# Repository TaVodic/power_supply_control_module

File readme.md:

# Laboratory Power Supply Control Module (PSCM)   

Module is an upgarde for Nice-Power SPS305 0-30V/0-5A laboratory power supply. Module use encoders instead of potentiometers. Based on ATmega328PB.
Using arduino-cli framework.  
### Features:
* Encoders EC12E, fine and coarse set of volatge and current
* Digital potentiometers MCP4251
* ATmega328PB
* Sniffing the PS voltage, current and power - providing a feedback
* UART connection for PC connection and automated PS setting

### Libraries used:
* Encoder_mt, [original](https://github.com/PaulStoffregen/Encoder) modified to use PCINT and optimized for the use-case
* DispSniff, sniffing SDI & CLK pins of TM1640 (of the original PS) to capture voltage, current and power values of the PS
* MCP4251, [original](https://github.com/kulbhushanchand/MCP4251)

## [Schematic v1.0.0](docu/pscm_schematic_v1.0.0.pdf)

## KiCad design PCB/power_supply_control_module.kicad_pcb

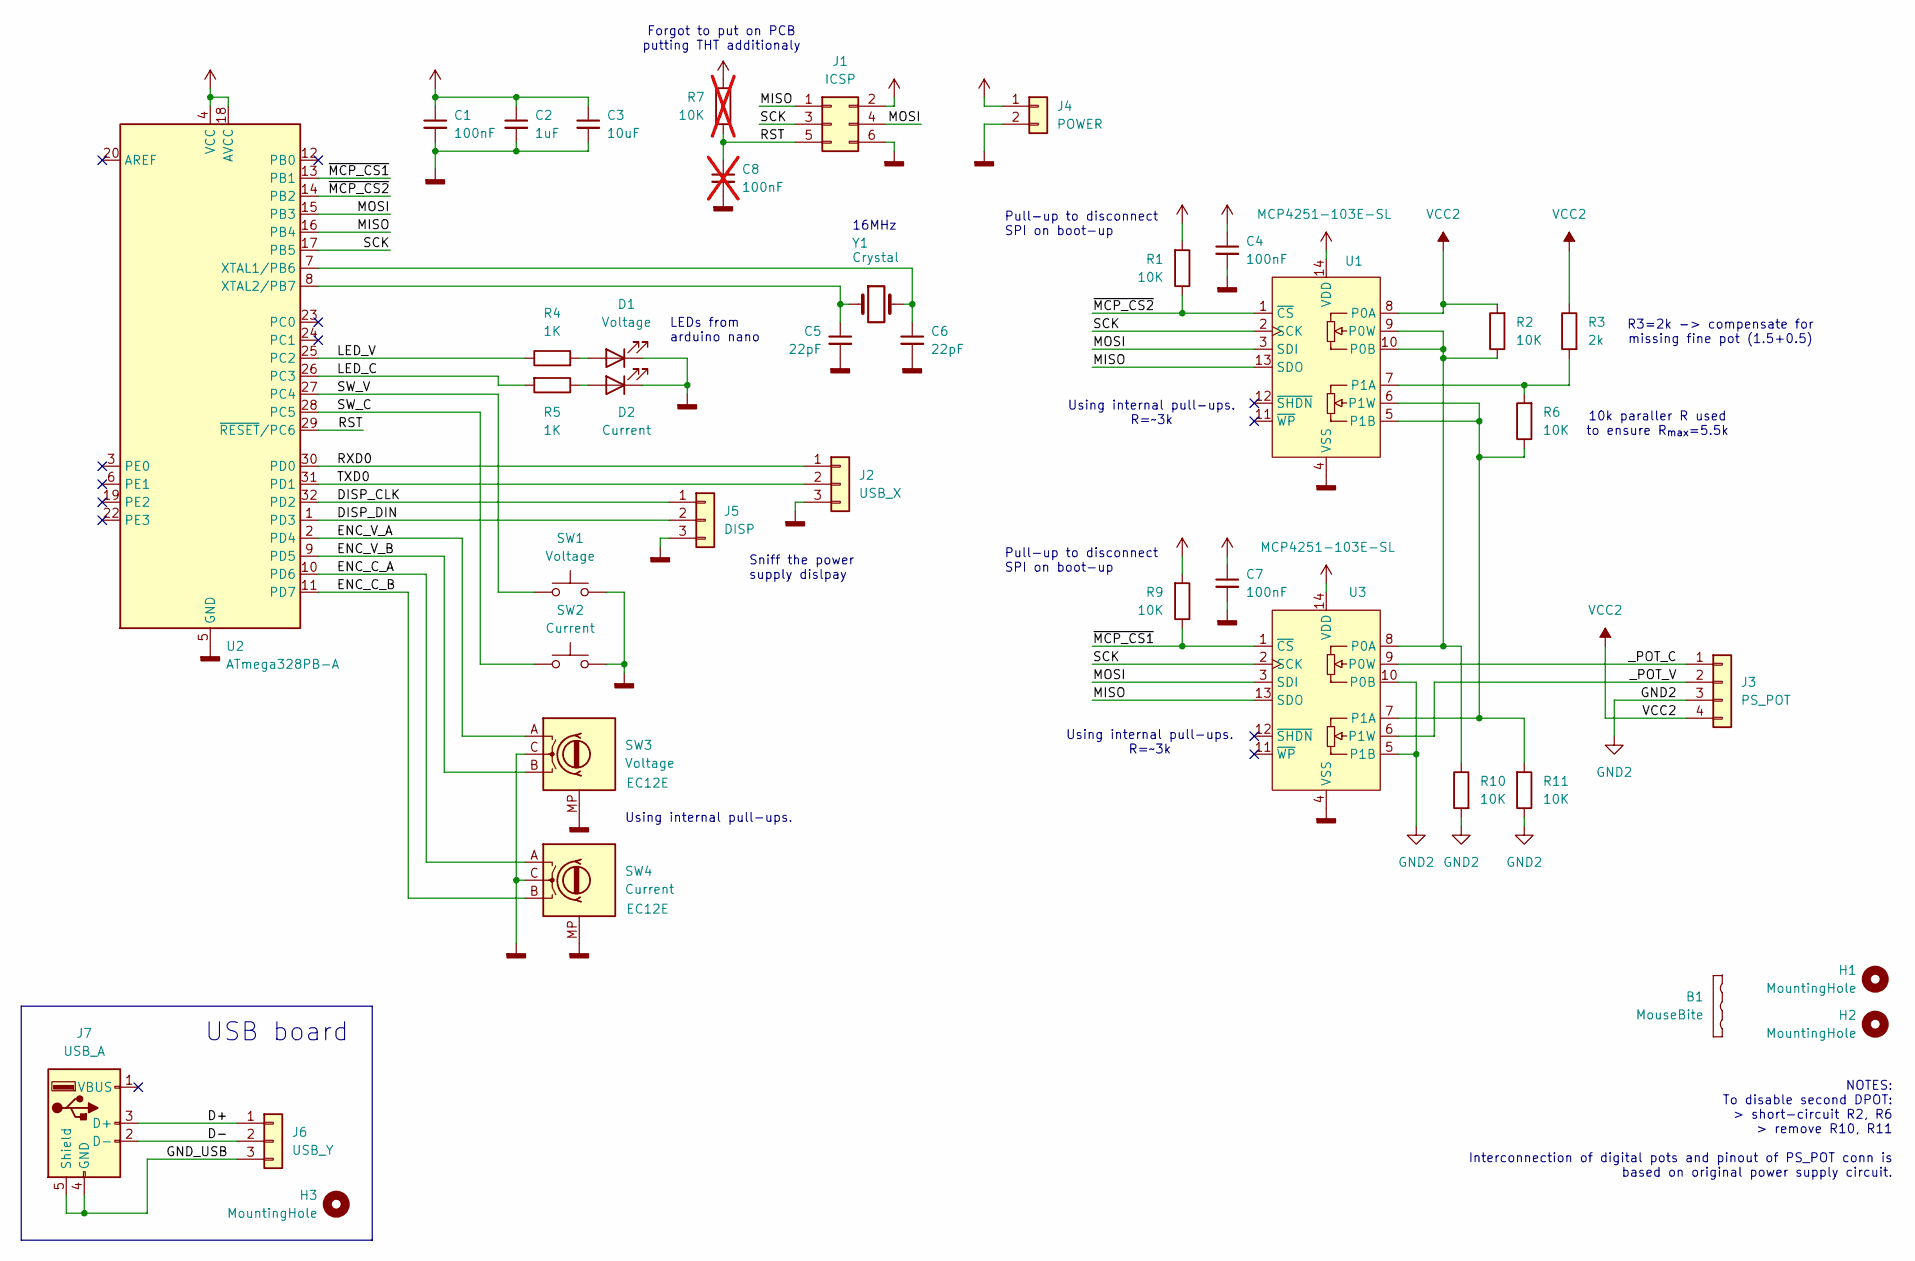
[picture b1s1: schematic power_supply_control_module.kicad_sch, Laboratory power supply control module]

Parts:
B1: MouseBite; mouse-bite-3mm-slot-jlcpcb
C1, C4, C7: 100nF; C_1206_3216Metric_Pad1.33x1.80mm_HandSolder
C2: 1uF; C_1206_3216Metric_Pad1.33x1.80mm_HandSolder
C3: 10uF; C_1206_3216Metric_Pad1.33x1.80mm_HandSolder
C5, C6: 22pF; C_1206_3216Metric_Pad1.33x1.80mm_HandSolder
C8: 100nF; C_1206_3216Metric_Pad1.33x1.80mm_HandSolder; not fitted
D1: Voltage; LED_0603_1608Metric_Pad1.05x0.95mm_HandSolder
D2: Current; LED_0603_1608Metric_Pad1.05x0.95mm_HandSolder
H1, H2, H3: MountingHole; MountingHole_3.2mm_M3_ISO7380
J1: ICSP; PinHeader_2x03_P2.54mm_Vertical
J2: USB_X; SHDR3W50P0X200_1X3_800X470X640P
J3: PS_POT; JST_XH_B4B-XH-A_1x04_P2.50mm_Vertical
J4: POWER; 140502415001
J5: DISP; SHDR3W50P0X200_1X3_800X470X640P
J6: USB_Y; PinHeader_1x03_P2.00mm_Vertical
J7: USB_A; USB_A_Molex_105057_Vertical
R1, R2, R6, R9, R10, R11: 10K; R_1206_3216Metric_Pad1.30x1.75mm_HandSolder
R3: 2k; R_1206_3216Metric_Pad1.30x1.75mm_HandSolder
R4, R5: 1K; R_1206_3216Metric_Pad1.30x1.75mm_HandSolder
R7: 10K; R_1206_3216Metric_Pad1.30x1.75mm_HandSolder; not fitted
SW1: Voltage; SW_TH_Tactile_Omron_B3F-107x
SW2: Current; SW_TH_Tactile_Omron_B3F-107x
SW3: Voltage; RotaryEncoder_Alps_EC12E_Vertical_H20mm
SW4: Current; RotaryEncoder_Alps_EC12E_Vertical_H20mm
U1, U3: MCP4251-103E-SL; SOIC-14_3.9x8.7mm_P1.27mm
U2: ATmega328PB-A; TQFP-32_7x7mm_P0.8mm
Y1: Crystal; Crystal_HC49-4H_Vertical

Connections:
/D+: J6.1, J7.3 (D+)
/D-: J6.2, J7.2 (D-)
/DISP_CLK: J5.1, U2.32 (PD2)
/DISP_DIN: J5.2, U2.1 (PD3)
/ENC_C_A: SW4.A, U2.10 (PD6)
/ENC_C_B: SW4.B, U2.11 (PD7)
/ENC_V_A: SW3.A, U2.2 (PD4)
/ENC_V_B: SW3.B, U2.9 (PD5)
/GND_USB: J6.3, J7.4 (GND), J7.5 (Shield)
/LED_C: R5.2, U2.26 (PC3)
/LED_V: R4.1, U2.25 (PC2)
/MISO: J1.1, U1.13 (SDO), U2.16 (PB4), U3.13 (SDO)
/MOSI: J1.4, U1.3 (SDI), U2.15 (PB3), U3.3 (SDI)
/RST: C8.1, J1.5, R7.1, U2.29 (~RESET/PC6)
/RXD0: J2.1, U2.30 (PD0)
/SCK: J1.3, U1.2 (SCK), U2.17 (PB5), U3.2 (SCK)
/SW_C: SW2.1, U2.28 (PC5)
/SW_V: SW1.1, U2.27 (PC4)
/TXD0: J2.2, U2.31 (PD1)
/_POT_C: J3.1, U3.9 (P0W)
/_POT_V: J3.2, U3.6 (P1W)
/~MCP_CS1: R9.1, U2.13 (PB1), U3.1 (~CS)
/~MCP_CS2: R1.1, U1.1 (~CS), U2.14 (PB2)
GND2: J3.3, R10.2, R11.1, U3.5 (P1B), U3.10 (P0B)
GNDD: C1.2, C2.2, C3.2, C4.2, C5.2, C6.2, C7.2, C8.2, D1.1 (K), D2.1 (K), J1.6, J2.3, J4.2, J5.3, SW1.2, SW2.2, SW3.C, SW3.MP, SW4.C, SW4.MP, U1.4 (VSS), U2.5 (GND), U2.21 (GND), U3.4 (VSS)
unnamed: D1.2 (A), R4.2
unnamed: D2.2 (A), R5.1
unnamed: R2.1, R10.1, U1.9 (P0W), U1.10 (P0B), U3.8 (P0A)
unnamed: R3.2, R6.2, U1.7 (P1A)
unnamed: R6.1, R11.2, U1.5 (P1B), U1.6 (P1W), U3.7 (P1A)
unnamed: C6.1, U2.7 (XTAL1/PB6), Y1.2
unnamed: C5.1, U2.8 (XTAL2/PB7), Y1.1
VCC: C1.1, C2.1, C3.1, C4.1, C7.1, J1.2, J4.1, R1.2, R7.2, R9.2, U1.14 (VDD), U2.4 (VCC), U2.18 (AVCC), U3.14 (VDD)
VCC2: J3.4, R2.2, R3.1, U1.8 (P0A)

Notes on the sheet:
Forgot to put on PCB putting THT additionaly
Using internal pull-ups. R=~3k
Pull-up to disconnect SPI on boot-up
10k paraller R used to ensure R_{max}=5.5k
NOTES: To disable second DPOT: > short-circuit R2, R6 > remove R10, R11 Interconnection of digital pots and pinout of PS_POT conn is based on original power supply circuit.
Using internal pull-ups.
R3=2k -> compensate for missing fine pot (1.5+0.5)
16MHz
USB board
Sniff the power supply dislpay
LEDs from arduino nano

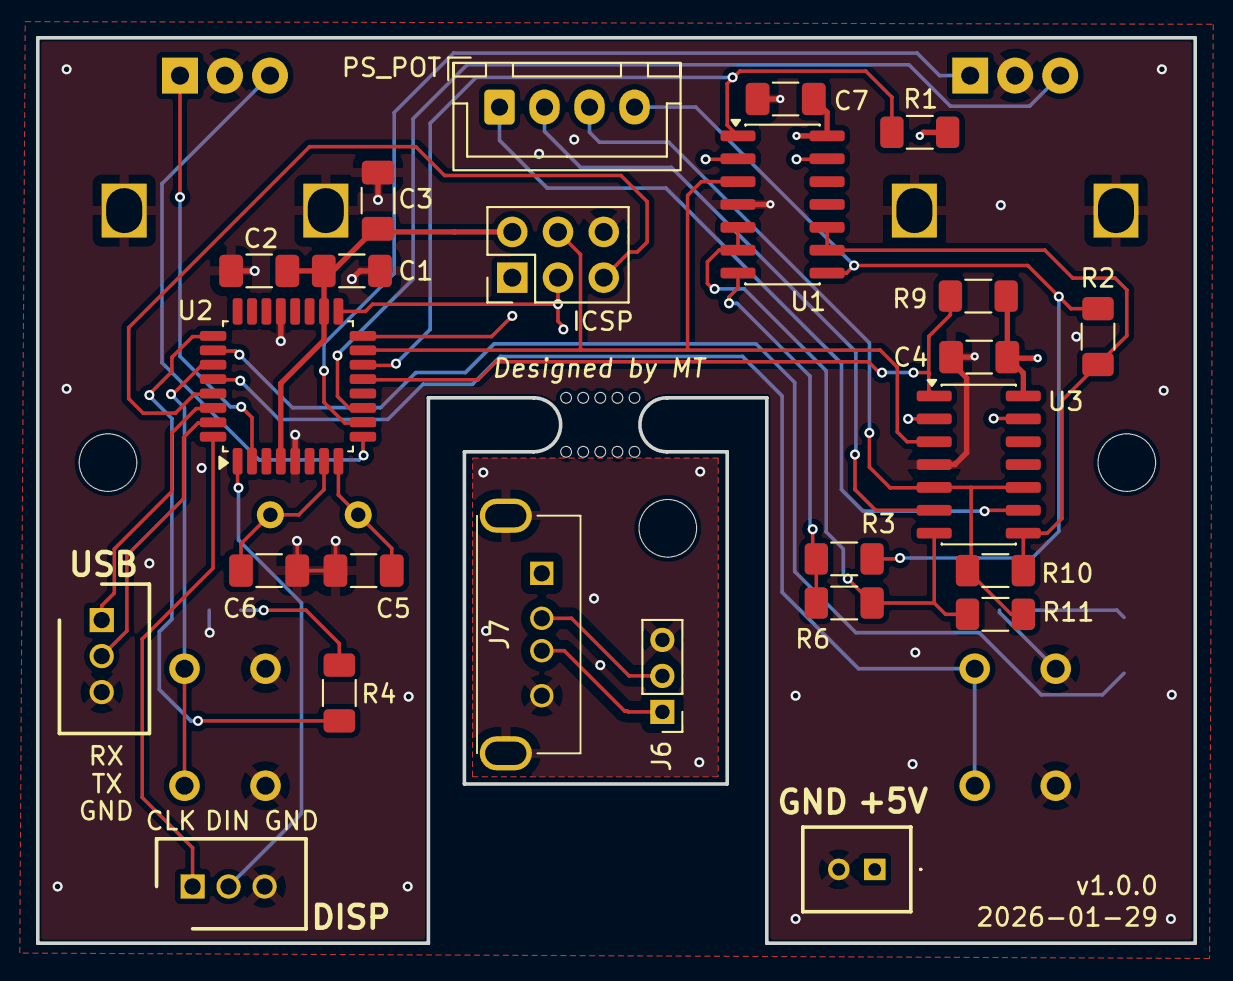
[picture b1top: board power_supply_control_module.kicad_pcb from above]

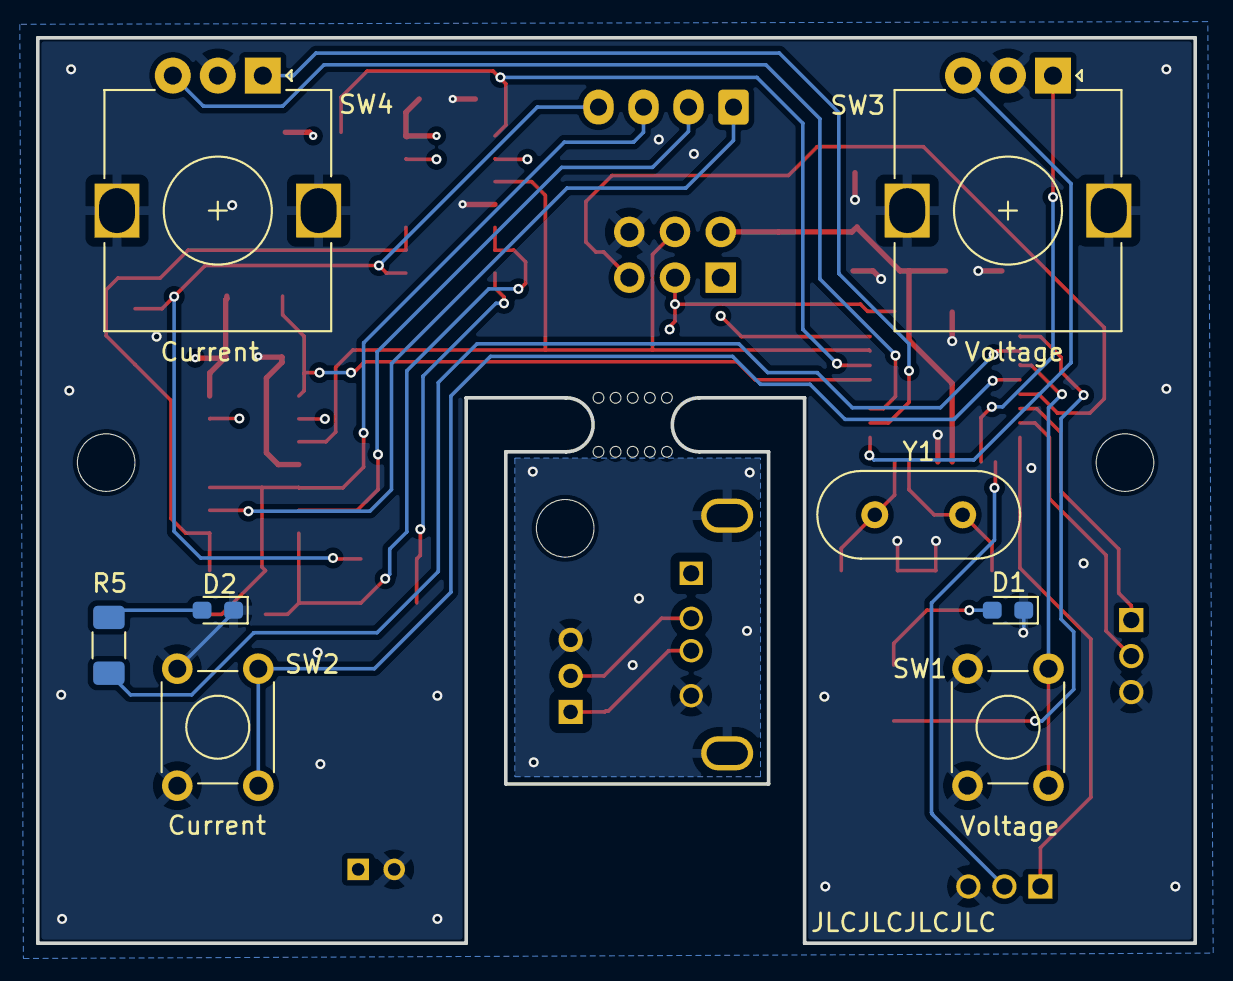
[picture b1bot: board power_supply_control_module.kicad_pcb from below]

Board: 4 copper layers, 64.3 x 50.3 mm, 37 parts (8 on the bottom side), 34 nets.

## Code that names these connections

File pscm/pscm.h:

#ifndef PSCM_H
#define PSCM_H

#ifdef __cplusplus
extern "C" {
#endif

#define READ_DPIN(dp) (*portInputRegister(digitalPinToPort(dp)) & digitalPinToBitMask(dp))

#define BTN_DEBOUNCE_MS 200
#define COARSE_RES      4
#define WIPERS_MAX_VAL  488 // limited to 30V
#define WIPER_MAX_VAL   256
#define SER_BUFF_SIZE   20

#define pin_MCP_CS1 9  // PB1
#define pin_MCP_CS2 10 // PB2
#define pin_MOSI    11 // PB3
#define pin_MISO    12 // PB4
#define pin_SCK     13 // PB5
#define pin_LED_V   16 // PC2
#define pin_LED_C   17 // PC3
#define pin_SW_V    18 // PC4 PCINT12
#define pin_SW_C    19 // PC5 PCINT13
#define pin_ENC_V_A 4  // PD4 PCINT20
#define pin_ENC_V_B 5  // PD5 PCINT21
#define pin_ENC_C_A 6  // PD6 PCINT22
#define pin_ENC_C_B 7  // PD7 PCINT23

// Fixed pins for classic ATmega328P/328PB Arduino boards:
// CLK -> PD2 (INT0 / Arduino D2) DISPSNIFF_CLK_PIN_PORTD
// DIN -> PD3 (INT1 / Arduino D3) DISPSNIFF_DIN_PIN_PORTD

#ifdef __cplusplus
}
#endif

#endif

// white - MCU TX
// green - MCU RX

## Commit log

2026-01-25 init
2026-01-25 PCB project created
2026-01-25 schematic and board WIP
2026-01-26 second MCP added WIP
2026-01-26 Schematic finished
2026-01-26 FW project created
2026-01-26 PCB WIP
2026-01-27 disp sniffer lib added
2026-01-27 added USB PCB, before connecting the PCBs
2026-01-27 USB PCB finished
2026-01-28 routing finished
2026-01-28 PCB finished, JLCPCB ordered
2026-01-28 added forgotten RST pin treatement
2026-01-28 formating and intelisence settings updated
2026-01-29 [SW] refactoring, comments added
2026-01-29 [SW] trying to read int from disp
2026-01-30 [SW] keep only last frame WIP
2026-02-01 dispsniff lib working
2026-02-01 dispsniff.c optimized
2026-02-01 [SW] MCP lib added
2026-02-01 [SW] Encoder implementation, using INT0 & INT1
2026-02-02 [SW] one encoder working nice
2026-02-02 [SW] encoder working fine but uses INT and polling - not a good practise
2026-02-02 [SW] One encoder working perfectly
    - no polling, just PCINT
    - TIMER1 to debounce the pins, 600us gate
2026-02-02 [SW] Encoder pins treatement (only PD4-7)
2026-02-02 [SW] Optimization - interruptArgs[28] removed, only two ENC supported
2026-02-02 [SW] Two encoders perfectly working
2026-02-03 [SW] debounced buttons added
2026-02-03 [SW] UI WIP
2026-02-04 readme added
2026-02-11 upload.sh updated for atmega328pb
2026-02-17 buttons fixed
2026-02-17 encoder quandrature reading changed to single count when specific transition happen
2026-02-18 successfully setting voltage and current
2026-03-08 fuses and decrement issues repaired
2026-03-08 dual POT (resolution increase)
2026-03-08 bootloader burned, UART programming not working
2026-03-09 GUI added
2026-03-09 sending V and C setting
